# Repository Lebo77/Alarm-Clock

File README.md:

# Alarm-Clock
An ESP32 based alarm clock

This is a bedside alarm clock and light controller I developed. IT relies on a number of external libraries:

OpenWeather by Bodmer
  TFT_eSPI by Bodmer
  JSON_Decoder by Bodmer
  (Thanks Bodmer. This project would not be possible without you)
  ESP8266Audio by Earle F. Pillhower III
  NeoPixelBus by Makuna
  DS3232RTC by Jack Christensen
  Time by Paul Stoffregen
  The ESP32 Board support Package for Arduino by espressif

Thanks and credit to all of them. A few of these files are from Bodmer's libraries. They are included as that is how he intended for them to be employed in the project.

Also included in the KiCad Project directory are the PCB layout files and schematics I used to build my clock.

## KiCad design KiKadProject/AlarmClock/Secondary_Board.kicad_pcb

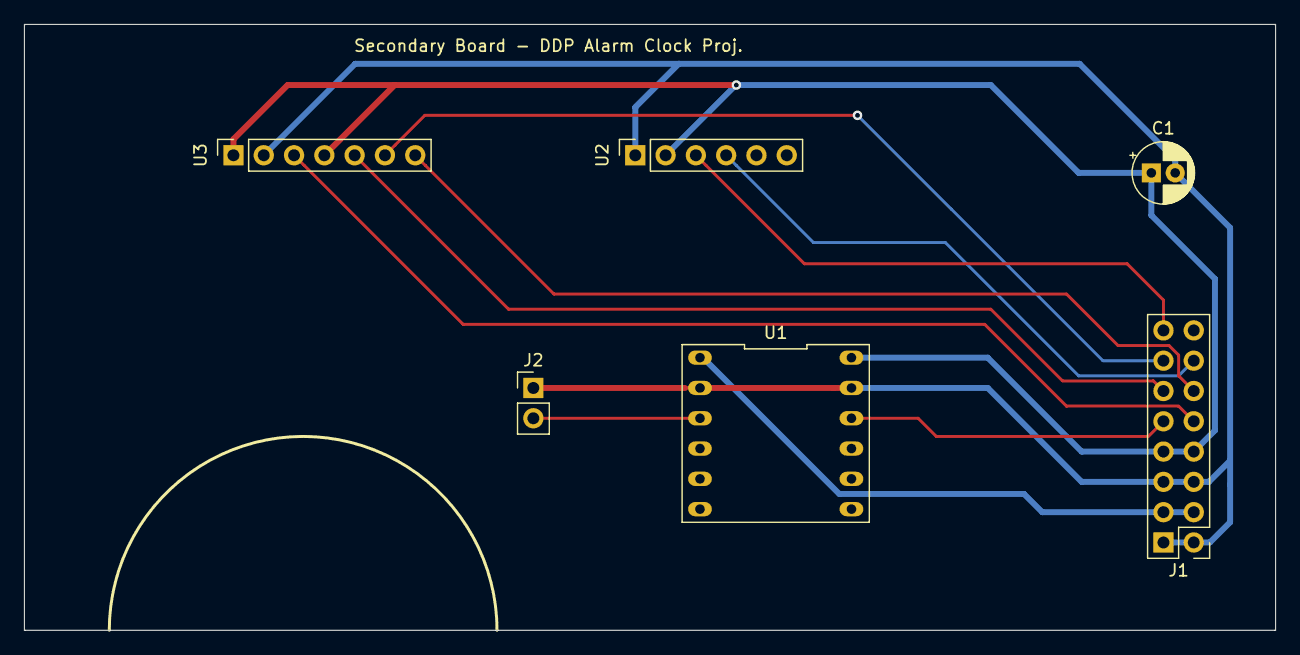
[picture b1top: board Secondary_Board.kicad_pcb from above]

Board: 2 copper layers, 104.9 x 50.8 mm, 6 parts (0 on the bottom side), 11 nets.

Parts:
C1: 100uF; CP_Radial_D5.0mm_P2.00mm
J1: Conn_to_Main_Board; PinHeader_2x08_P2.54mm_Vertical_REV
J2: LED_CTRL; PinHeader_1x02_P2.54mm_Vertical
U1: LOGIC_LVL_CVTR_4X; LOGIC_LVL_CVTR_X4
U2: DS3231_BREAKOUT; PinSocket_1x06_P2.54mm_Vertical
U3: MAX98357A_BREAKOUT; PinSocket_1x07_P2.54mm_Vertical

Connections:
+3V3: C1.1, J1.7, J1.8, U1.12, U2.2, U3.1, U3.4
+5V: J1.3, J1.4, U1.1
/AUDIO_BCLK: J1.13, U3.6
/AUDIO_DIN: J1.11, U3.5
/AUDIO_LRC: J1.12, U3.7
/AUDIO_SD: J1.10, U3.3
/I2C_SCL: J1.14, U2.4
/I2C_SDA: J1.15, U2.3
/LED_CTRL: J1.9, U1.10
/LED_CTRL_5V: J2.2, U1.3
GND: C1.2, J1.1, J1.2, J1.5, J1.6, J2.1, U1.2, U1.11, U2.1, U3.2

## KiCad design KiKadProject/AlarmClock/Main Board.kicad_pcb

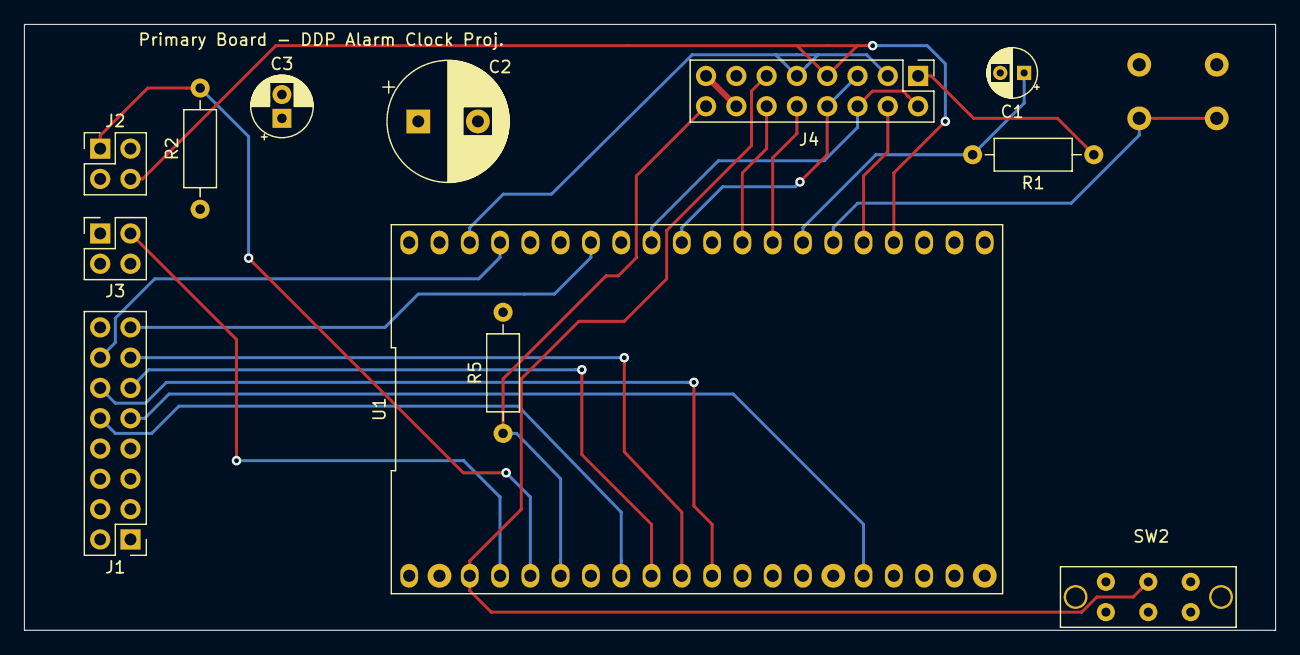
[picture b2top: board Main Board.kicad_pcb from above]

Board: 4 copper layers, 104.9 x 50.8 mm, 13 parts (1 on the bottom side), 24 nets.

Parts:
C1: CP_.1Uf; CP_Radial_D4.0mm_P2.00mm
C2: CP_1000uF; CP_Radial_D10.0mm_P5.00mm
C3: CP_220uF; CP_Radial_D5.0mm_P2.00mm
J1: Conn_to_Sec.Board; PinHeader_2x08_P2.54mm_Vertical
J2: SNOOZE_BUTTON; PinHeader_2x02_P2.54mm_Vertical
J3: Volume_Pot; PinHeader_2x02_P2.54mm_Vertical
J4: FRONT_PNL; PinHeader_2x08_P2.54mm_Vertical
R1: R_5k; R_Axial_DIN0207_L6.3mm_D2.5mm_P10.16mm_Horizontal
R2: R_US_5K; R_Axial_DIN0207_L6.3mm_D2.5mm_P10.16mm_Horizontal
R5: R_51K; R_Axial_DIN0207_L6.3mm_D2.5mm_P10.16mm_Horizontal
SW1: SW_Push_BOOT; SW_PUSH_6mm
SW2: SW_SPDT_POWER; SW_SK22H03_2P2T_RA
U1: ESP32-Dev-Board; ESP32_DEV_BOARD

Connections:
+3V3: C3.1, J1.7, J1.8, J3.1, J4.14, J4.15, R2.1, U1.1
+5V: C2.1, J1.3, J1.4, U1.19
/AUDIO_BCLK: J1.13, U1.9
/AUDIO_DIN: J1.11, U1.8
/AUDIO_LRC: J1.12, U1.10
/AUDIO_SD: J1.10, U1.7
/CS: J4.12, U1.28
/DC: J4.10, U1.27
/DIMMING: J2.4, J4.7, U1.23
/I2C_SCL: J1.14, U1.36
/I2C_SDA: J1.15, U1.33
/LED_CTRL: J1.9, U1.15
/LIGHT_SENSE: J4.16, R5.1, U1.5
/MISO: J4.2, J4.6, U1.31
/MOSI: J4.3, J4.9, U1.37
/RESET: J4.11, SW2.2, U1.2
/SCK: J4.5, J4.8, U1.30
/SNOOZE_SWITCH: J2.1, R2.2, U1.4
/T_CS: J4.4, U1.24
/T_IRQ: J4.1, R1.1
/VOLUME_SIG: J3.2, U1.3
GND: C1.2, C2.2, C3.2, J1.1, J1.2, J1.5, J1.6, J2.2, J2.3, J3.3, J4.13, R5.2, SW1.2, SW2.3, U1.14, U1.32, U1.38
unnamed: C1.1, R1.2, U1.26
unnamed: SW1.1, U1.25

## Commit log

2020-02-01 Adding schematic
2020-02-01 Updated. Added photos and schematic
2020-03-11 Fixed DST
2022-02-08 Version 0.5
    Update to latest Revision. Significant bugfixes and improvements.
2022-02-08 Adding Board layout files and schematics.
